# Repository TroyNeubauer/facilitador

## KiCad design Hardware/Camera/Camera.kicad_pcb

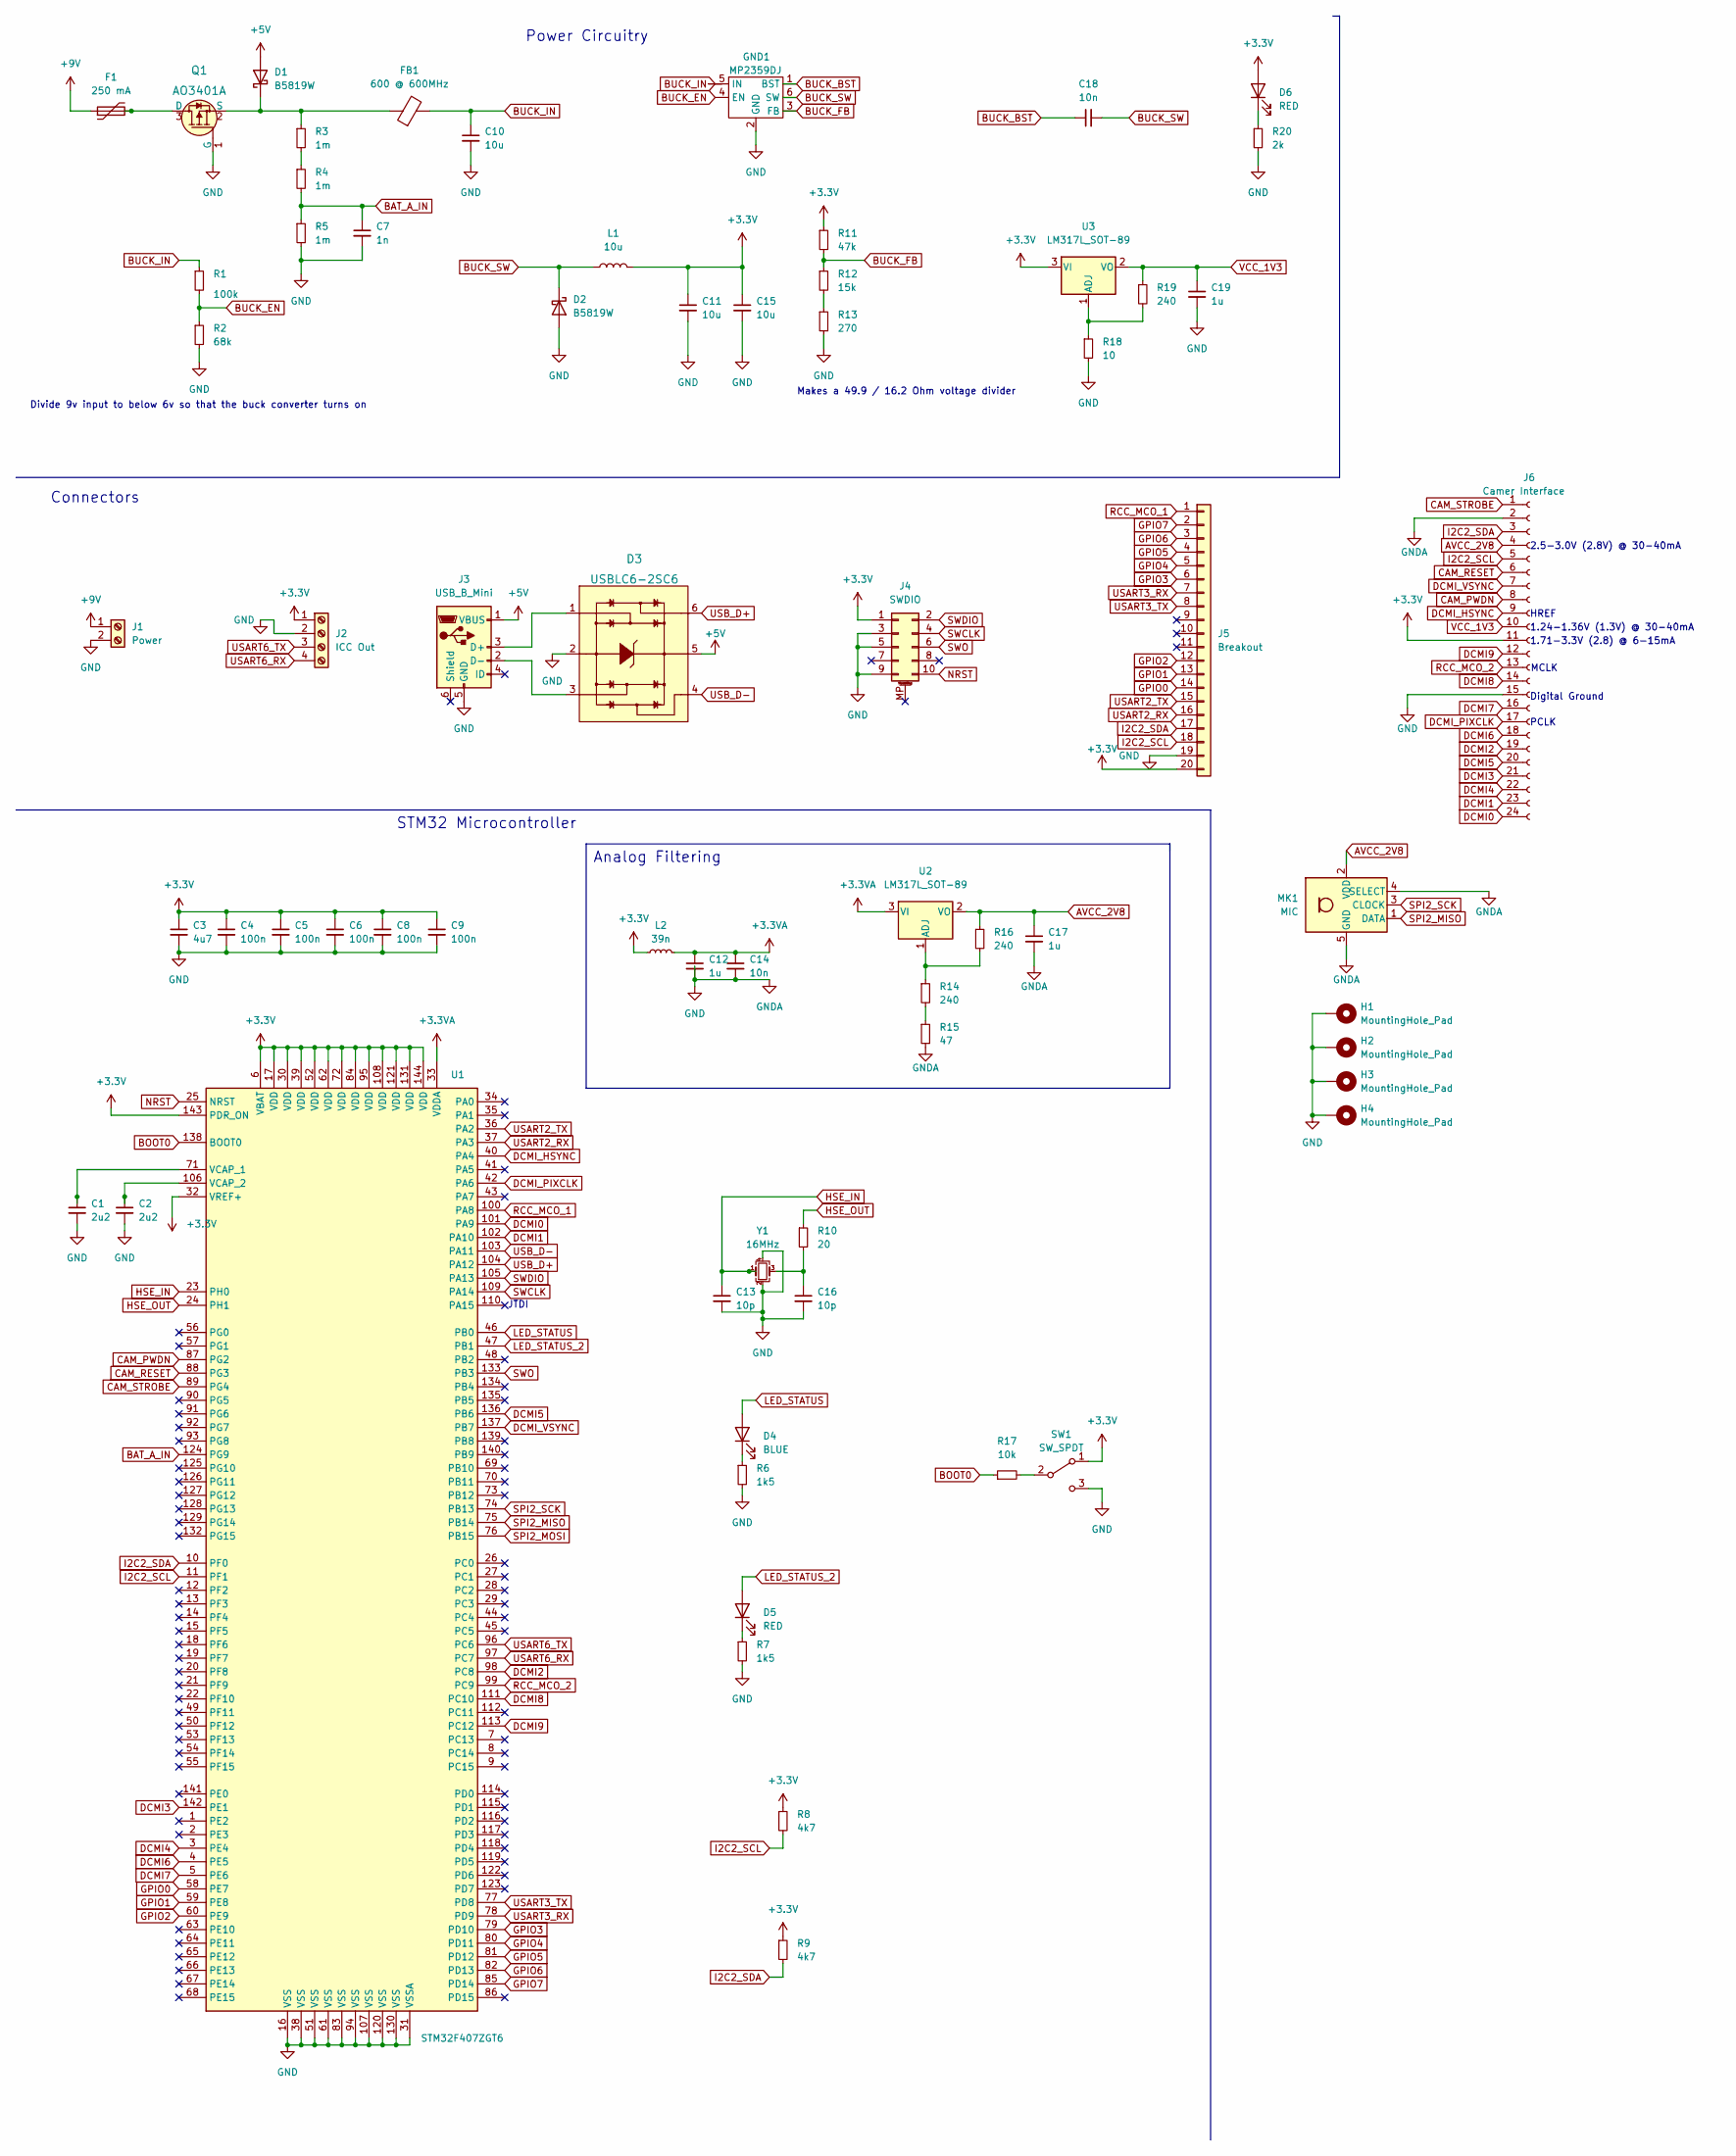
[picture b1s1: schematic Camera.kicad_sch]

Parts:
C1, C2: 2u2; C_0603_1608Metric
C3: 4u7; C_0603_1608Metric
C4, C5, C6, C8, C9: 100n; C_0402_1005Metric
C7: 1n; C_0603_1608Metric
C10, C11, C15: 10u; C_1206_3216Metric
C12, C17, C19: 1u; C_0402_1005Metric
C13, C16: 10p; C_0402_1005Metric
C14: 10n; C_0402_1005Metric
C18: 10n; C_1206_3216Metric
D1, D2: B5819W; D_SOD-123
D3: USBLC6-2SC6; SOT23-6L; MPN USBLC6-2SC6; Digi-Key_PN 497-5235-1-ND
D4: BLUE; LED_0603_1608Metric
D5, D6: RED; LED_0603_1608Metric
F1: 250 mA; Fuse_1206_3216Metric
FB1: 600 @ 600MHz; L_0805_2012Metric
GND1: MP2359DJ; SOT-23-6
H1, H2, H3, H4: MountingHole_Pad; MountingHole_4.3mm_M4_Pad_Via
J1: Power; TerminalBlock_Phoenix_PT-1,5-2-3.5-H_1x02_P3.50mm_Horizontal
J2: ICC Out; TerminalBlock_Phoenix_PT-1,5-4-3.5-H_1x04_P3.50mm_Horizontal
J3: USB_B_Mini; USB_Micro-B_Molex-105133-0031
J4: SWDIO; PinSocket_2x05_P1.27mm_Vertical_SMD
J5: Breakout; PinHeader_1x20_P1.27mm_Vertical
J6: Camer Interface; SAMTEC_ZF5S-24-01-T-WT
L1: 10u; L_6.3x6.3_H3
L2: 39n; L_0603_1608Metric
MK1: MIC; Infineon_PG-LLGA-5-1
Q1: AO3401A; MPN AO3401A; Digi-Key_PN 785-1001-1-ND
R1: 100k; R_0603_1608Metric
R2: 68k; R_0603_1608Metric
R3, R4, R5: 1m; R_0603_1608Metric
R6, R7: 1k5; R_0603_1608Metric
R8, R9: 4k7; R_0402_1005Metric
R10: 20; R_0402_1005Metric
R11: 47k; R_0603_1608Metric
R12: 15k; R_0603_1608Metric
R13: 270; R_0603_1608Metric
R14, R16, R19: 240; R_0603_1608Metric
R15: 47; R_0603_1608Metric
R17: 10k; R_0402_1005Metric
R18: 10; R_0603_1608Metric
R20: 2k; R_0603_1608Metric
SW1: SW_SPDT; SW_SPDT_PCM12
U1: STM32F407ZGT6; LQFP-144_20x20mm_P0.5mm
U2, U3: LM317L_SOT-89; SOT-89-3
Y1: 16MHz; Crystal_SMD_3225-4Pin_3.2x2.5mm

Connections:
+3.3VA: C12.1, C14.1, L2.2, U1.33 (VDDA), U2.3 (VI)
+3V3: C3.1, C4.1, C5.1, C6.1, C8.1, C9.1, C11.1, C15.1, D6.2 (A), J2.1, J4.1, J5.20, J6.11, L1.2, L2.1, R8.1, R9.1, R11.1, SW1.1 (A), U1.6 (VBAT), U1.17 (VDD), U1.30 (VDD), U1.32 (VREF+), U1.39 (VDD), U1.52 (VDD), U1.62 (VDD), U1.72 (VDD), U1.84 (VDD), U1.95 (VDD), U1.108 (VDD), U1.121 (VDD), U1.131 (VDD), U1.143 (PDR_ON), U1.144 (VDD), U3.3 (VI)
+5V: D1.2 (A), D3.5, J3.1 (VBUS)
+9V: F1.1, J1.1
AVCC_2V8: C17.1, J6.4, MK1.2 (VDD), R16.1, U2.2 (VO)
BAT_A_IN: C7.1, R4.2, R5.1, U1.124 (PG9)
BOOT0: R17.1, U1.138 (BOOT0)
BUCK_BST: C18.1, GND1.1 (BST)
BUCK_EN: GND1.4 (EN), R1.2, R2.1
BUCK_FB: GND1.3 (FB), R11.2, R12.1
BUCK_IN: C10.1, FB1.2, GND1.5 (IN), R1.1
BUCK_SW: C18.2, D2.1 (K), GND1.6 (SW), L1.1
CAM_PWDN: J6.8, U1.87 (PG2)
CAM_RESET: J6.6, U1.88 (PG3)
CAM_STROBE: J6.1, U1.89 (PG4)
DCMI0: J6.24, U1.101 (PA9)
DCMI1: J6.23, U1.102 (PA10)
DCMI2: J6.19, U1.98 (PC8)
DCMI3: J6.21, U1.142 (PE1)
DCMI4: J6.22, U1.3 (PE4)
DCMI5: J6.20, U1.136 (PB6)
DCMI6: J6.18, U1.4 (PE5)
DCMI7: J6.16, U1.5 (PE6)
DCMI8: J6.14, U1.111 (PC10)
DCMI9: J6.12, U1.113 (PC12)
DCMI_HSYNC: J6.9, U1.40 (PA4)
DCMI_PIXCLK: J6.17, U1.42 (PA6)
DCMI_VSYNC: J6.7, U1.137 (PB7)
GND: C1.2, C2.2, C3.2, C4.2, C5.2, C6.2, C7.2, C8.2, C9.2, C10.2, C11.2, C12.2, C13.2, C14.2, C15.2, C16.2, C17.2, C19.2, D2.2 (A), D3.2, GND1.2 (GND), H1.1, H2.1, H3.1, H4.1, J1.2, J2.2, J3.5 (GND), J4.3, J4.5, J4.9, J5.19, J6.2, J6.15, MK1.4 (SELECT), MK1.5 (GND), Q1.1 (G), R2.2, R5.2, R6.2, R7.2, R13.2, R15.2, R18.2, R20.2, SW1.3 (C), U1.16 (VSS), U1.31 (VSSA), U1.38 (VSS), U1.51 (VSS), U1.61 (VSS), U1.83 (VSS), U1.94 (VSS), U1.107 (VSS), U1.120 (VSS), U1.130 (VSS), Y1.2, Y1.4
GPIO0: J5.14, U1.58 (PE7)
GPIO1: J5.13, U1.59 (PE8)
GPIO2: J5.12, U1.60 (PE9)
GPIO3: J5.6, U1.79 (PD10)
GPIO4: J5.5, U1.80 (PD11)
GPIO5: J5.4, U1.81 (PD12)
GPIO6: J5.3, U1.82 (PD13)
GPIO7: J5.2, U1.85 (PD14)
HSE_IN: C13.1, U1.23 (PH0), Y1.1
HSE_OUT: R10.1, U1.24 (PH1)
I2C2_SCL: J5.18, J6.5, R8.2, U1.11 (PF1)
I2C2_SDA: J5.17, J6.3, R9.2, U1.10 (PF0)
LED_STATUS: D4.2 (A), U1.46 (PB0)
LED_STATUS_2: D5.2 (A), U1.47 (PB1)
NRST: J4.10, U1.25 (NRST)
unnamed: C1.1, U1.71 (VCAP_1)
unnamed: C2.1, U1.106 (VCAP_2)
unnamed: C16.1, R10.2, Y1.3
unnamed: D1.1 (K), FB1.1, Q1.2 (S), R3.1
unnamed: D3.1, J3.3 (D+)
unnamed: D3.3, J3.2 (D-)
unnamed: D4.1 (K), R6.1
unnamed: D5.1 (K), R7.1
unnamed: D6.1 (K), R20.1
unnamed: F1.2, Q1.3 (D)
unnamed: R3.2, R4.1
unnamed: R12.2, R13.1
unnamed: R14.1, R16.2, U2.1 (ADJ)
unnamed: R14.2, R15.1
unnamed: R17.2, SW1.2 (B)
unnamed: R18.1, R19.2, U3.1 (ADJ)
RCC_MCO_1: J5.1, U1.100 (PA8)
RCC_MCO_2: J6.13, U1.99 (PC9)
SPI2_MISO: MK1.1 (DATA), U1.75 (PB14)
SPI2_MOSI: U1.76 (PB15)
SPI2_SCK: MK1.3 (CLOCK), U1.74 (PB13)
SWCLK: J4.4, U1.109 (PA14)
SWDIO: J4.2, U1.105 (PA13)
SWO: J4.6, U1.133 (PB3)
USART2_RX: J5.16, U1.37 (PA3)
USART2_TX: J5.15, U1.36 (PA2)
USART3_RX: J5.7, U1.78 (PD9)
USART3_TX: J5.8, U1.77 (PD8)
USART6_RX: J2.4, U1.97 (PC7)
USART6_TX: J2.3, U1.96 (PC6)
USB_D+: D3.6, U1.104 (PA12)
USB_D-: D3.4, U1.103 (PA11)
VCC_1V3: C19.1, J6.10, R19.1, U3.2 (VO)

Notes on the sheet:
Makes a 49.9 / 16.2 Ohm voltage divider
JTDI
HREF
1.71-3.3V (2.8) @ 6-15mA
STM32 Microcontroller
Power Circuitry
MCLK
Digital Ground
Divide 9v input to below 6v so that the buck converter turns on
Analog Filtering
PCLK
2.5-3.0V (2.8V) @ 30-40mA
1.24-1.36V (1.3V) @ 30-40mA
Connectors

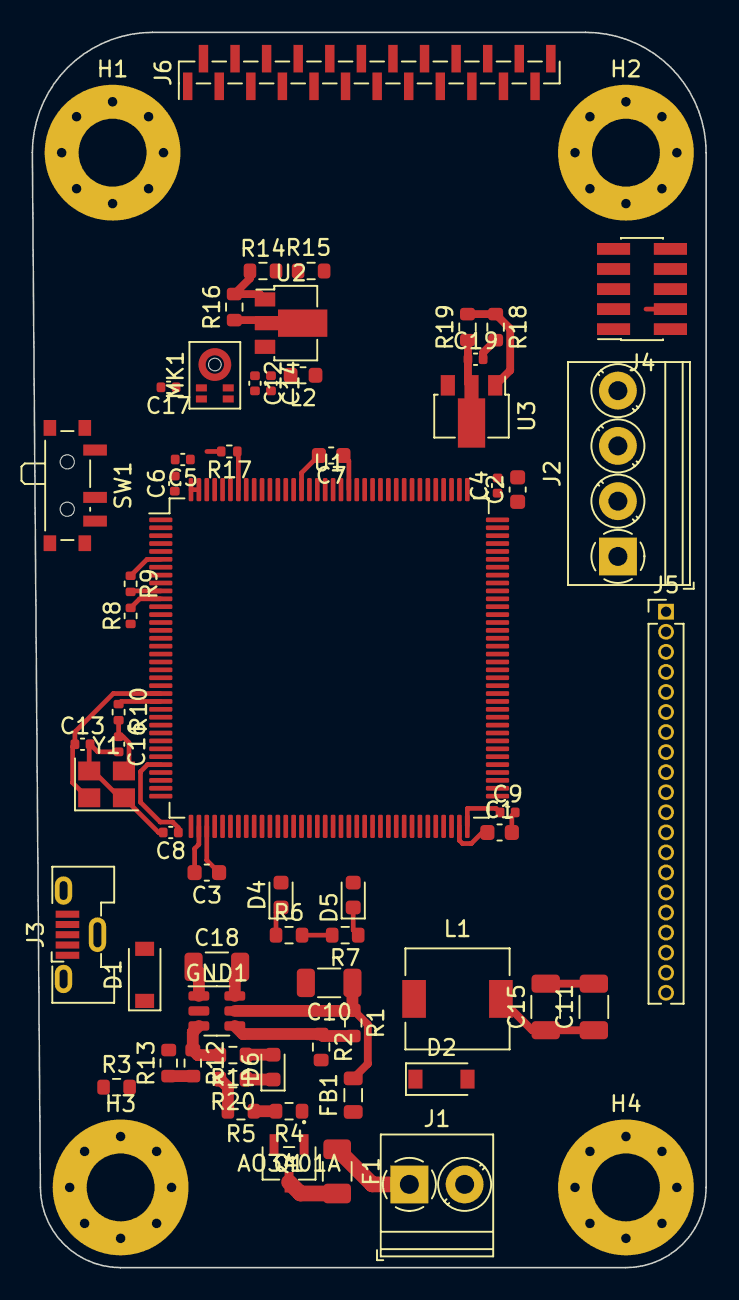
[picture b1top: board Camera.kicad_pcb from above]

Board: 4 copper layers, 42.7 x 78.2 mm, 66 parts (0 on the bottom side), 72 nets.

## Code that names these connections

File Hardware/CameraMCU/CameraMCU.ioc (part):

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Mcu.Name=STM32F407Z(E-G)Tx
Mcu.Package=LQFP144
Mcu.UserName=STM32F407ZGTx
PA11.Mode=Device_Only
PA11.Signal=USB_OTG_FS_DM
PA12.Mode=Device_Only
PA12.Signal=USB_OTG_FS_DP
PA13.Mode=JTAG_5_pins
PA13.Signal=SYS_JTMS-SWDIO
PA14.Mode=JTAG_5_pins
PA14.Signal=SYS_JTCK-SWCLK
PA15.Mode=JTAG_5_pins
PA15.Signal=SYS_JTDI
PA2.Mode=Asynchronous
PA2.Signal=USART2_TX
PA3.Mode=Asynchronous
PA3.Signal=USART2_RX
PA4.Mode=Slave_10_bits_External_Synchro
PA4.Signal=DCMI_HSYNC
PA5.Mode=Simplex_Bidirectional_Master
PA5.Signal=SPI1_SCK
PA6.Mode=Slave_10_bits_External_Synchro
PA6.Signal=DCMI_PIXCLK
PA7.Mode=Simplex_Bidirectional_Master
PA7.Signal=SPI1_MOSI
PB10.Mode=Full_Duplex_Master
PB10.Signal=SPI2_SCK
PB11.Mode=Asynchronous
PB11.Signal=USART3_RX
PB3.Mode=JTAG_5_pins
PB3.Signal=SYS_JTDO-SWO
PB4.Mode=JTAG_5_pins
PB4.Signal=SYS_JTRST
PB6.Mode=Slave_10_bits_External_Synchro
PB6.Signal=DCMI_D5
PB7.Mode=Slave_10_bits_External_Synchro
PB7.Signal=DCMI_VSYNC
PC10.Mode=Slave_10_bits_External_Synchro
PC10.Signal=DCMI_D8
PC12.Mode=Slave_10_bits_External_Synchro
PC12.Signal=DCMI_D9
PC2.Mode=Full_Duplex_Master
PC2.Signal=SPI2_MISO
PC3.Mode=Full_Duplex_Master
PC3.Signal=SPI2_MOSI
PC6.Mode=Slave_10_bits_External_Synchro
PC6.Signal=DCMI_D0
PC7.Mode=Slave_10_bits_External_Synchro
PC7.Signal=DCMI_D1
PC8.Mode=Slave_10_bits_External_Synchro
PC8.Signal=DCMI_D2
PC9.Mode=Slave_10_bits_External_Synchro
PC9.Signal=DCMI_D3
PD8.Mode=Asynchronous
PD8.Signal=USART3_TX
PE4.Mode=Slave_10_bits_External_Synchro
PE4.Signal=DCMI_D4
PE5.Mode=Slave_10_bits_External_Synchro
PE5.Signal=DCMI_D6
PE6.Mode=Slave_10_bits_External_Synchro
PE6.Signal=DCMI_D7
PF0.Mode=I2C
PF0.Signal=I2C2_SDA
PF1.Mode=I2C
PF1.Signal=I2C2_SCL
PG14.Mode=Asynchronous
PG14.Signal=USART6_TX
PG9.Mode=Asynchronous
PG9.Signal=USART6_RX
PH0-OSC_IN.Mode=HSE-External-Oscillator
PH0-OSC_IN.Signal=RCC_OSC_IN
PH1-OSC_OUT.Mode=HSE-External-Oscillator
PH1-OSC_OUT.Signal=RCC_OSC_OUT
RCC.HSE_VALUE=25000000
RCC.SYSCLKFreq_VALUE=16000000
board=custom

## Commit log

2022-02-01 Finished initial positioning!
2022-02-02 Small improvements for pre-routing
2022-02-07 Init radio test projects and camera software
2022-02-07 Update TX program
2022-02-08 Radio tx works!
2022-02-08 Found issue. Must connect Chip enable pin to do TX and RX
2022-02-10 Encryption tests failing
2022-02-10 Made sure key is aligned
2022-02-11 Refactored key to key.rs
2022-02-12 Finished crypt test
2022-02-13 Working on making wordsize more generic
2022-02-21 Finalized algorithm
2022-02-22 Finished 28 byte plaintext abstraction
2022-02-22 Adding USB decode support
2022-02-24 Optimizing camera placement
2022-03-01 Finished initial placement
2022-03-01 Basic routing done
2022-03-01 About to re-do layout

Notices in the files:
parts and their libraries:
Copyright 2021 Accelerated Designs. All rights reserved.
